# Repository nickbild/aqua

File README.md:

# Aqua

Aqua turns the underpowered Mattel Aquarius into a respectable computer by adding 32 KB of RAM and SD card mass storage.

The Mattel Aquarius home computer was released in June of 1983 and had already been discontinued by October of that same year.  The short lifespan of this machine is no big surprise — it is equipped with 4 KB of RAM, which is reduced to 1.7 KB of free RAM after factoring in the reserved video memory and system variables.  It also has a terrible rubber chiclet keyboard that is not quite large enough for adult hands.  But despite these (and many more!) flaws, beyond all reason, I still love this computer so I wanted to give mine a little help.  By adding 32 KB of additional memory it is much more usable, and the SD card reader allows me to write software on a modern machine, then easily load it onto the Aquarius, which means I don't have to try to type in long programs on its awful keyboard (or use the cassette port, which is slow and fails far more than it succeeds).

## How It Works

The Aqua PCB ([KiCad files here](https://github.com/nickbild/aqua/tree/main/aqua_pcb)) is designed to plug into the cartridge port of the Aquarius.  It has a 32 KB SRAM chip and logic chips to map it into the 32K addresses above onboard memory ($4000-$BFFF).  It also has a pin header that gives easy access to the cartridge port's connectors.  These are quite useful since the computer offers hardly any other options for extension, and the cartridge port offers direct, unbuffered access to the address and data bus, and virtually all other signals on the Z80.

Aqua brings the Aquarius closer to being in the same league as other contemporary computers, but there is still no decent way to load programs onto it — and using the computer's keyboard to type them is a terrible experience.  So I built AquaWrite, which connects to Aqua's pin header, to load programs/data into memory on the Aquarius from an SD card.  Using AquaWrite, it is possible to write and assemble programs on a modern computer, then write the machine code, as a sequence of newline-delimited bytes, to a text file.  That card can be inserted into AquaWrite and loaded into memory in a few seconds.

AquaWrite ([KiCad files here](https://github.com/nickbild/aqua/tree/main/aqua_write_pcb)) uses an Arduino Mega 2560 ([Arduino code here](https://github.com/nickbild/aqua/tree/main/aqua_write)) to handle SD card access and writing that data to a 1 KB dual-port SRAM chip.  That SRAM chip is mapped to addresses $FC00-$FFFF, and is used to transfer programs of any size into lower memory addresses in 1 KB pages.  The Arduino first writes a small (20 byte) program in machine code to the SRAM, then the next 1,004 bytes to be transferred.  When ready, the user is prompted to run a `USR` call that executes the machine code and transfers the bytes to a lower memory address.  This method is used because the Aquarius prevents access to addresses in the range of this SRAM from BASIC.  If the data to transfer exceeds 1004 bytes, the user presses a button on AquaWrite to load up each additional segment, then again runs `USR` to move the data to the next set of memory addresses.  Any size program (up to the limits of the Aquarius' memory) can be loaded in this way.

This is a bit more complicated because the Aquarius uses an early form of copy protection for external devices (anything that is not onboard the stock computer).  A PLA sits between the Z80 and data bus that XORs data with a software lock code (initialized to a random value on startup), which would scramble any values loaded via SD.  So before using AquaWrite for the first time after start up, a sequence of commands needs to run to disable this software lock:

```
poke 14510,63
poke 14412,63
poke 14530,63

10 print 1
run

poke 15250,175
poke 15251,211
poke 15252,255
poke 15253,201

poke 14341,59
poke 14340,146
x=usr(0)

poke 14510,191
poke 14412,191
poke 14530,191

run
```

This (temporarily) relocates the stack and other system variables to onboard memory (before the lock code is changed and they get scrambled), then runs a simple program that writes a `0` to the I/O port at $FF that stores the software lock code.  Since data is encoded/decoded by XORing it with the lock code, setting that code to `0` effectively turns it off — the result is always the same as the initial value.

Aqua:

AquaWrite:

## Media

The Aqua board, which adds 32 KB of SRAM and breaks the cartridge port connectors out into a pin header for easy access:

AquaWrite, which enables loading data from an SD card to Aquarius RAM:

## Bill of Materials

Aqua:
- Aqua PCB ([KiCad files here](https://github.com/nickbild/aqua/tree/main/aqua_pcb))
- 1 x 32 KB SRAM chip
- 1 x 74LS00
- 1 x 74LS86
- 1 x 74LS04
- 4 x 0.1 uF ceramic capacitors
- 1 x 1000 uF electrolytic capacitor
- 2 x 10mm M3 standoffs
- 2 x 15mm M3 standoffs
- 44 x male pin headers

AquaWrite:
- 1 x CY7C130-55PC 1 KB dual-port SRAM
- 1 x 74LS682
- 1 x 74LS32
- 1 x Arduino Mega 2560
- 1 x SD card breakout board
- 1 x 0.1 uF ceramic capacitors
- 1 x 47 uF electrolytic capacitor
- 1 x 10K ohm resistor
- 1 x pushbutton

## About the Author

[Nick A. Bild, MS](https://nickbild79.firebaseapp.com/#!/)

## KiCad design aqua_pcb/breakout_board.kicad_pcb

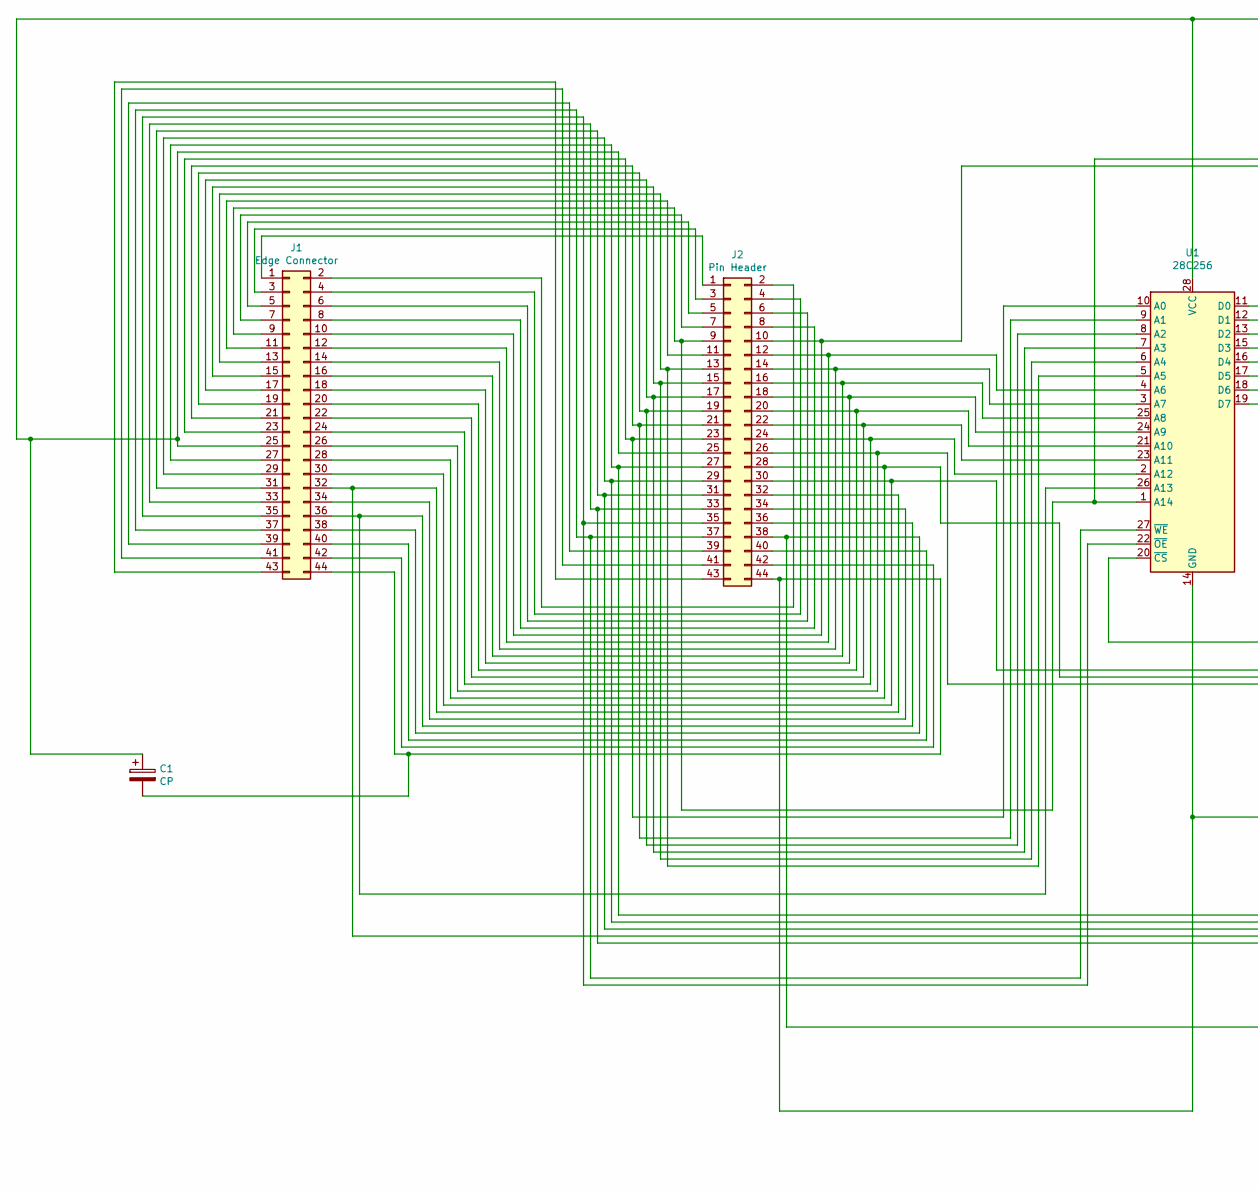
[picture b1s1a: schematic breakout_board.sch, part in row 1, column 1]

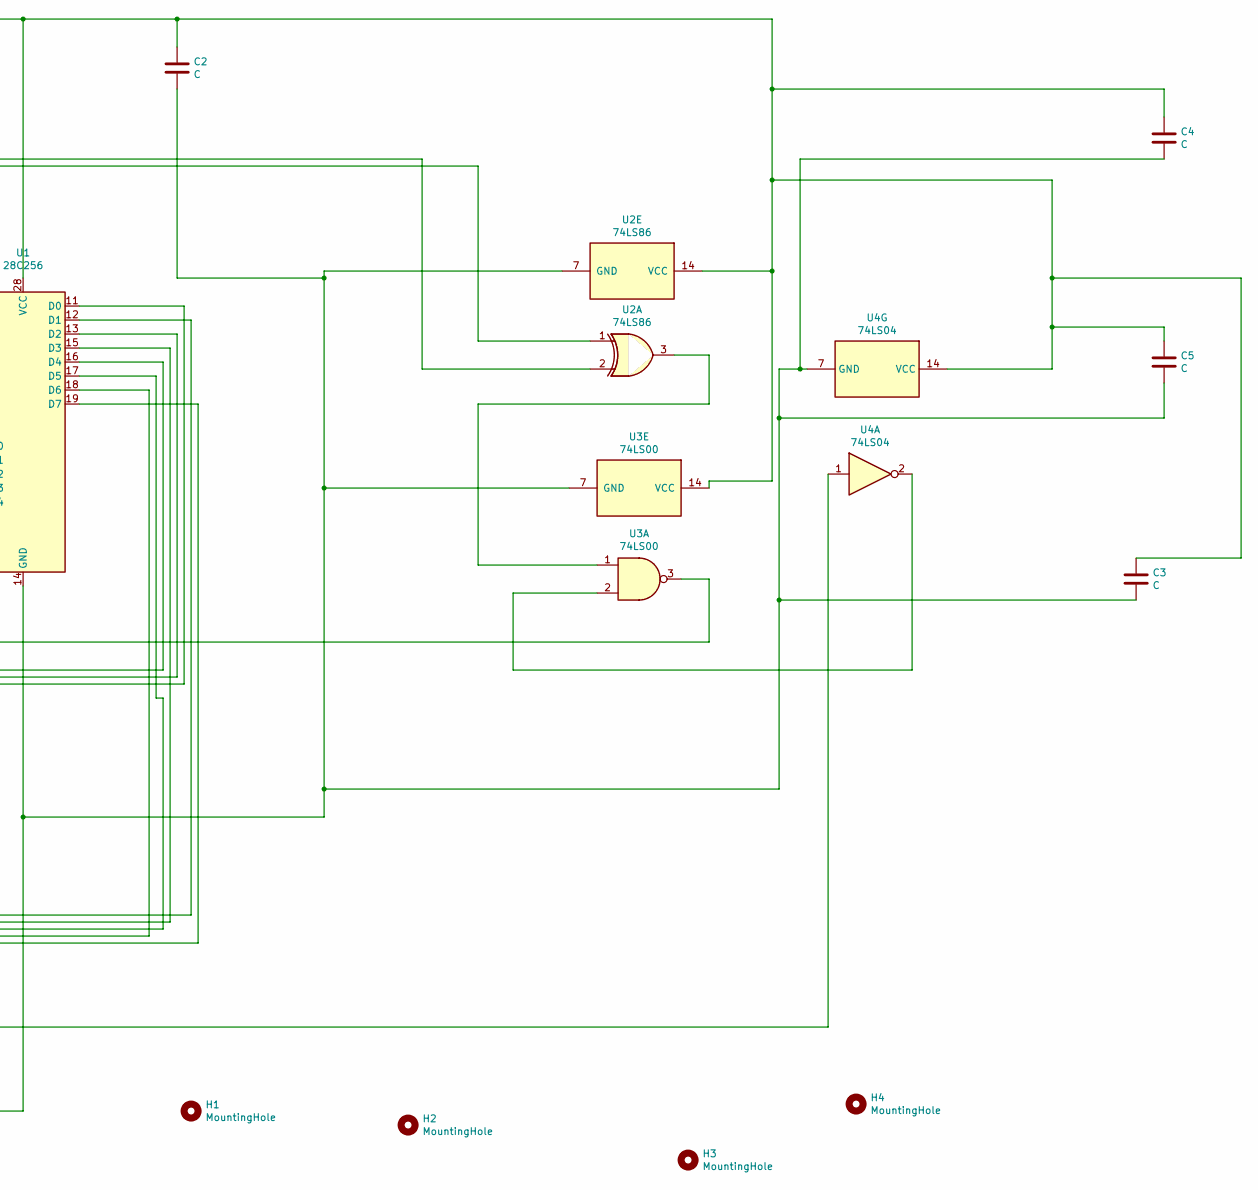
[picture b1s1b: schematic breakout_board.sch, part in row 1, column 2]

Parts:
C1: CP; CP_Radial_D14.0mm_P7.50mm
C2, C3, C4, C5: C; C_Disc_D4.3mm_W1.9mm_P5.00mm
H1, H2, H3, H4: MountingHole; MountingHole_3.2mm_M3
J1: Edge Connector; Aquarius_Cartridge
J2: Pin Header; PinSocket_2x22_P2.54mm_Vertical
U1: 28C256; DIP-28_W15.24mm
U2: 74LS86; DIP-14_W7.62mm
U3: 74LS00; DIP-14_W7.62mm
U4: 74LS04; DIP-14_W7.62mm

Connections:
unnamed: C1.1, C2.1, C3.1, C4.1, C5.1, J1.25, J2.25, U1.28 (VCC), U2.14 (VCC), U3.14 (VCC), U4.14 (VCC)
unnamed: C1.2, C2.2, C3.2, C4.2, C5.2, J1.44, J2.44, U1.14 (GND), U2.7 (GND), U3.7 (GND), U4.7 (GND)
unnamed: J1.1, J2.1
unnamed: J1.2, J2.2
unnamed: J1.3, J2.3
unnamed: J1.4, J2.4
unnamed: J1.5, J2.5
unnamed: J1.6, J2.6
unnamed: J1.7, J2.7
unnamed: J1.8, J2.8
unnamed: J1.9, J2.9, U1.1 (A14), U2.2
unnamed: J1.10, J2.10, U2.1
unnamed: J1.11, J2.11
unnamed: J1.12, J2.12, U1.4 (A6)
unnamed: J1.13, J2.13, U1.5 (A5)
unnamed: J1.14, J2.14, U1.3 (A7)
unnamed: J1.15, J2.15, U1.6 (A4)
unnamed: J1.16, J2.16, U1.25 (A8)
unnamed: J1.17, J2.17, U1.7 (A3)
unnamed: J1.18, J2.18, U1.24 (A9)
unnamed: J1.19, J2.19, U1.8 (A2)
unnamed: J1.20, J2.20, U1.21 (A10)
unnamed: J1.21, J2.21, U1.9 (A1)
unnamed: J1.22, J2.22, U1.23 (A11)
unnamed: J1.23, J2.23, U1.10 (A0)
unnamed: J1.24, J2.24, U1.2 (A12)
unnamed: J1.26, J2.26, U1.11 (D0)
unnamed: J1.27, J2.27, U1.12 (D1)
unnamed: J1.28, J2.28, U1.13 (D2)
unnamed: J1.29, J2.29, U1.15 (D3)
unnamed: J1.30, J2.30, U1.16 (D4)
unnamed: J1.31, J2.31, U1.17 (D5)
unnamed: J1.32, J2.32, U1.18 (D6)
unnamed: J1.33, J2.33, U1.19 (D7)
unnamed: J1.34, J2.34
unnamed: J1.35, J2.35, U1.22 (~OE)
unnamed: J1.36, J2.36, U1.26 (A13)
unnamed: J1.37, J2.37, U1.27 (~WE)
unnamed: J1.38, J2.38, U4.1
unnamed: J1.39, J2.39
unnamed: J1.40, J2.40
unnamed: J1.41, J2.41
unnamed: J1.42, J2.42
unnamed: J1.43, J2.43
unnamed: U1.20 (~CS), U3.3
unnamed: U2.3, U3.1
unnamed: U3.2, U4.2

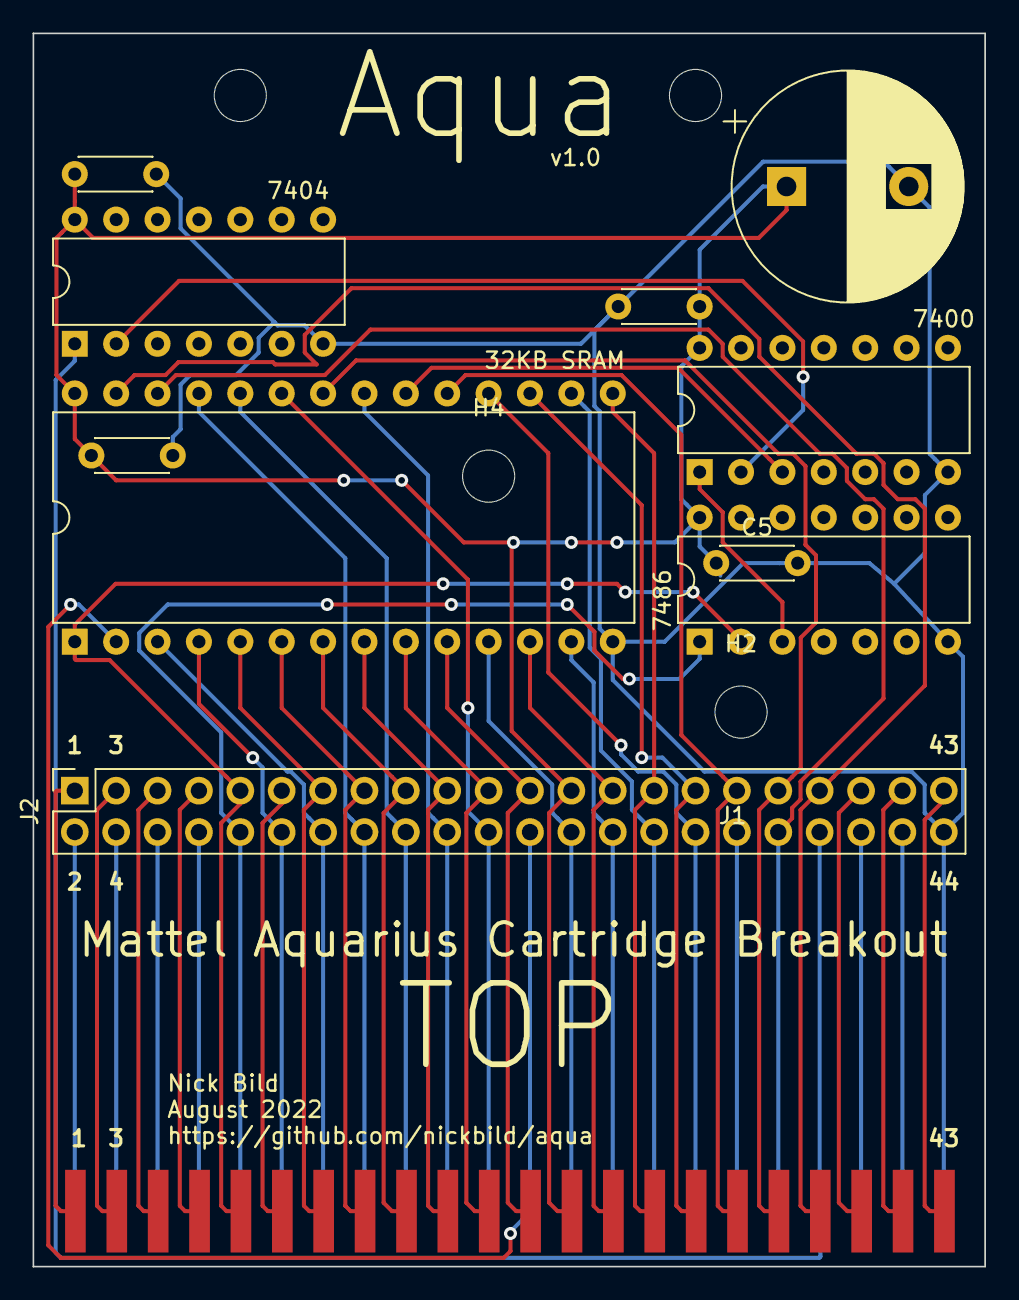
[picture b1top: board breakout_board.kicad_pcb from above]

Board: 2 copper layers, 58.4 x 75.7 mm, 15 parts (0 on the bottom side), 47 nets.

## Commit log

2022-08-20 Read SD card and write bytes sequentially to SRAM.
2022-08-20 Update documentation.
2022-08-21 Add debugging output.
2022-08-21 Simplify CE signal.
2022-08-21 Add pushbutton and bus disconnect logic.
2022-08-22 Add logic for starting on Aquarius bus.
2022-08-30 Add KiCad files.
2022-08-30 Remove old gerbers.
2022-09-05 Add Z80 machine code parsing and memory copying code.
2022-09-12 Add gerbers.
2022-09-12 Add SD card support.
2022-09-12 Test to dual-port RAM.
2022-09-12 Work on memory loader code.
2022-09-12 Finish RAM loader routine.
2022-09-23 Disable the external device encryption.
2022-09-23 Fix loop.
2022-09-23 Clean up.
2022-09-23 Update loader.
2022-09-24 Add schematic SVG.
